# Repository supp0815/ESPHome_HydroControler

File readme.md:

# Hydroponic Controller with ESPHome and HomeAssistant Dashboard

## System Setup

### Hardware

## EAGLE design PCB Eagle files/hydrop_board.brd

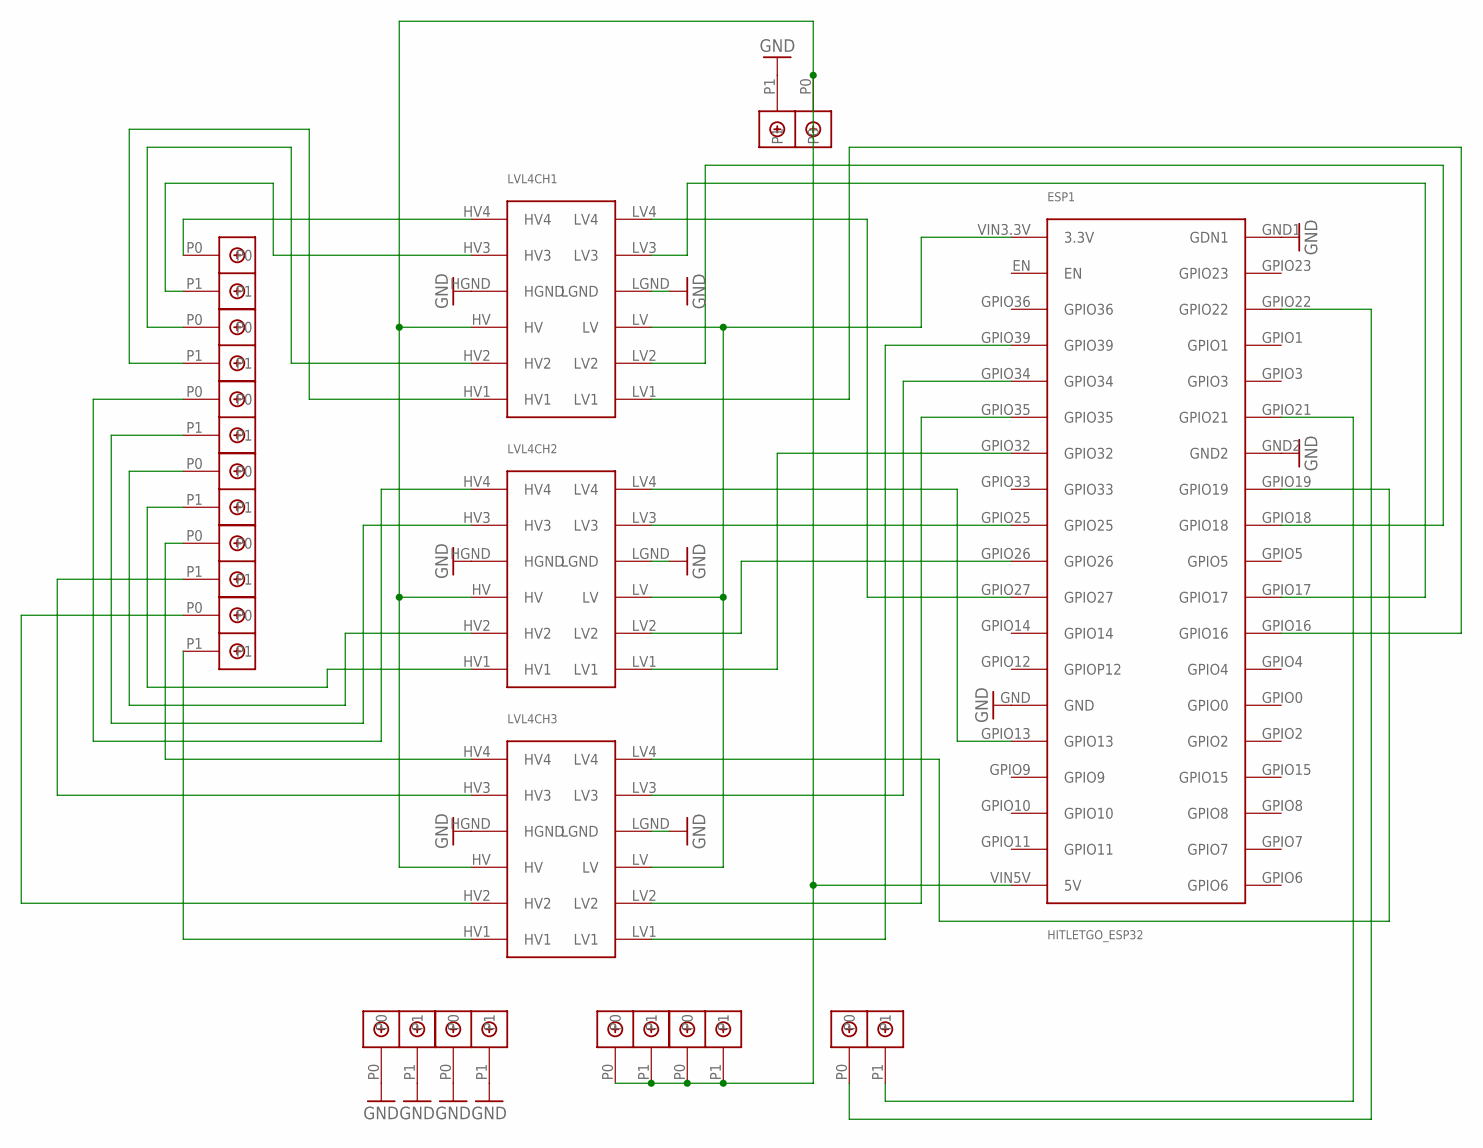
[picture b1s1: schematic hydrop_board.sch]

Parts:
ESP1: HITLETGO_ESP32; HILETGO_ESP32
LVL4CH1, LVL4CH2, LVL4CH3: LEVELSHIFTER_4CH
U$1, U$2, U$3, U$4, U$5, U$6, U$7, U$8, U$9, U$10, U$11, U$12: DBCONN-1X2

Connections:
GND: ESP1.GND, ESP1.GND1 (GDN1), ESP1.GND2, LVL4CH1.HGND, LVL4CH1.LGND, LVL4CH2.HGND, LVL4CH2.LGND, LVL4CH3.HGND, LVL4CH3.LGND, U$7.P1, U$8.P0, U$8.P1, U$9.P0, U$9.P1
unnamed: ESP1.GPIO22, U$12.P0
unnamed: ESP1.VIN3.3V (3.3V), LVL4CH1.LV, LVL4CH2.LV, LVL4CH3.LV
unnamed: ESP1.GPIO21, U$12.P1
unnamed: ESP1.GPIO27, LVL4CH1.LV4
unnamed: LVL4CH1.HV4, U$1.P0
unnamed: ESP1.GPIO17, LVL4CH1.LV3
unnamed: LVL4CH1.HV3, U$1.P1
unnamed: ESP1.GPIO18, LVL4CH1.LV2
unnamed: LVL4CH1.HV2, U$2.P0
unnamed: ESP1.GPIO16, LVL4CH1.LV1
unnamed: ESP1.VIN5V (5V), LVL4CH1.HV, LVL4CH2.HV, LVL4CH3.HV, U$7.P0, U$10.P0, U$10.P1, U$11.P0, U$11.P1
unnamed: LVL4CH1.HV1, U$2.P1
unnamed: ESP1.GPIO13, LVL4CH2.LV4
unnamed: LVL4CH2.HV4, U$3.P0
unnamed: ESP1.GPIO25, LVL4CH2.LV3
unnamed: LVL4CH2.HV3, U$3.P1
unnamed: ESP1.GPIO26, LVL4CH2.LV2
unnamed: LVL4CH2.HV2, U$4.P0
unnamed: ESP1.GPIO32, LVL4CH2.LV1
unnamed: LVL4CH2.HV1, U$4.P1
unnamed: ESP1.GPIO19, LVL4CH3.LV4
unnamed: LVL4CH3.HV4, U$5.P0
unnamed: ESP1.GPIO34, LVL4CH3.LV3
unnamed: LVL4CH3.HV3, U$5.P1
unnamed: ESP1.GPIO35, LVL4CH3.LV2
unnamed: LVL4CH3.HV2, U$6.P0
unnamed: ESP1.GPIO39, LVL4CH3.LV1
unnamed: LVL4CH3.HV1, U$6.P1

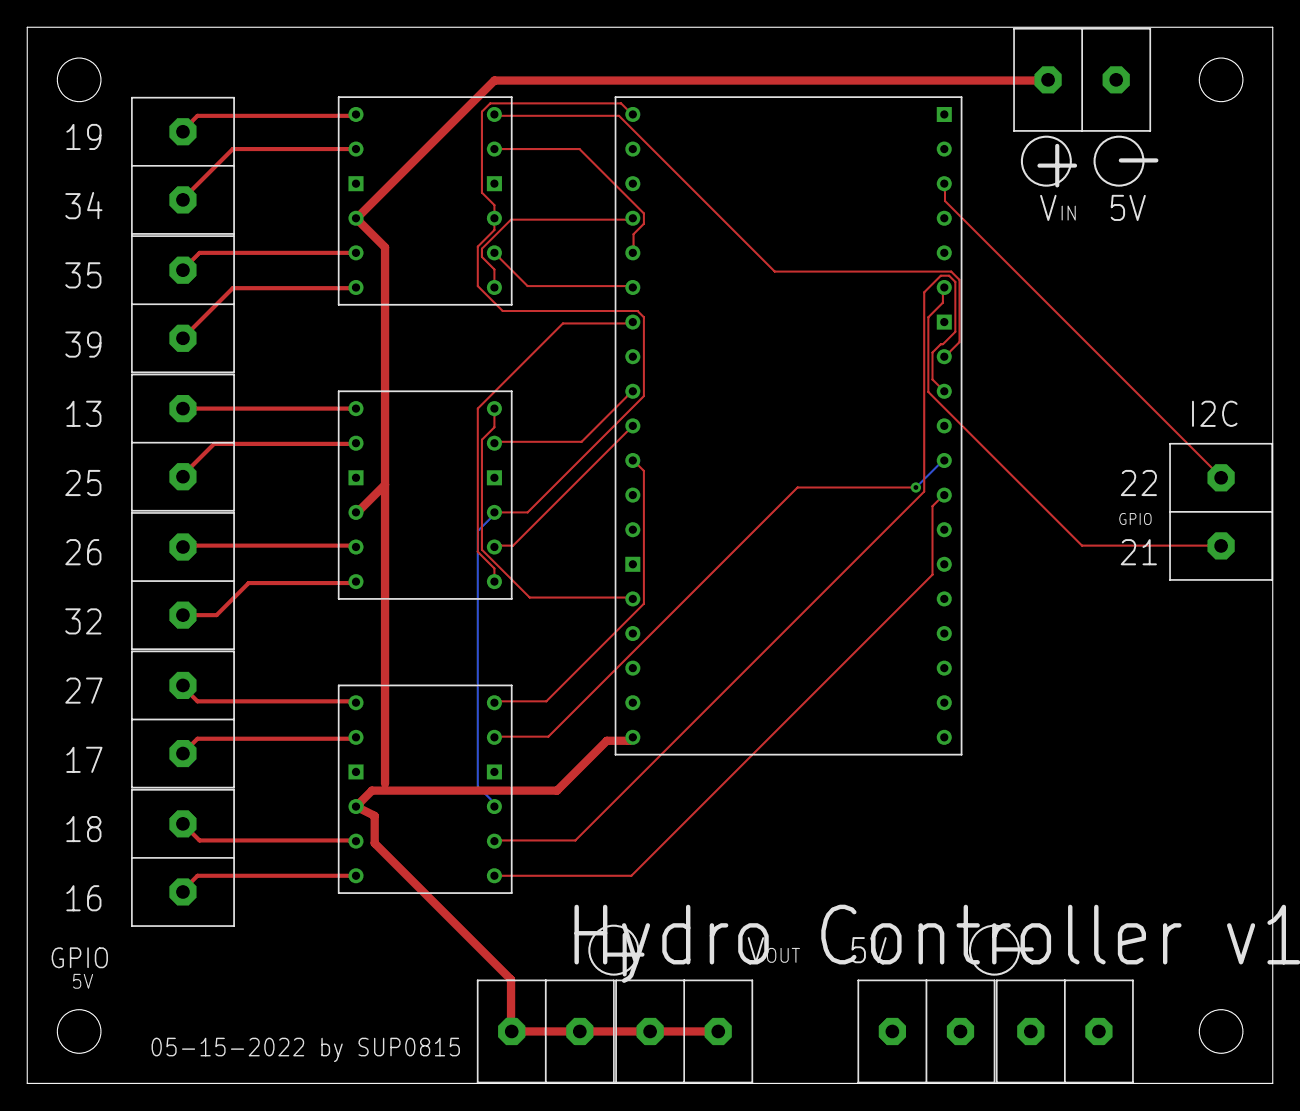
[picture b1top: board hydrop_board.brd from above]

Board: 2 copper layers, 91.4 x 77.5 mm, 16 parts (0 on the bottom side), 29 nets.

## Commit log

2022-05-27 Create media
2022-05-27 Create new
2022-05-27 Create libraries
2022-05-27 Create d
